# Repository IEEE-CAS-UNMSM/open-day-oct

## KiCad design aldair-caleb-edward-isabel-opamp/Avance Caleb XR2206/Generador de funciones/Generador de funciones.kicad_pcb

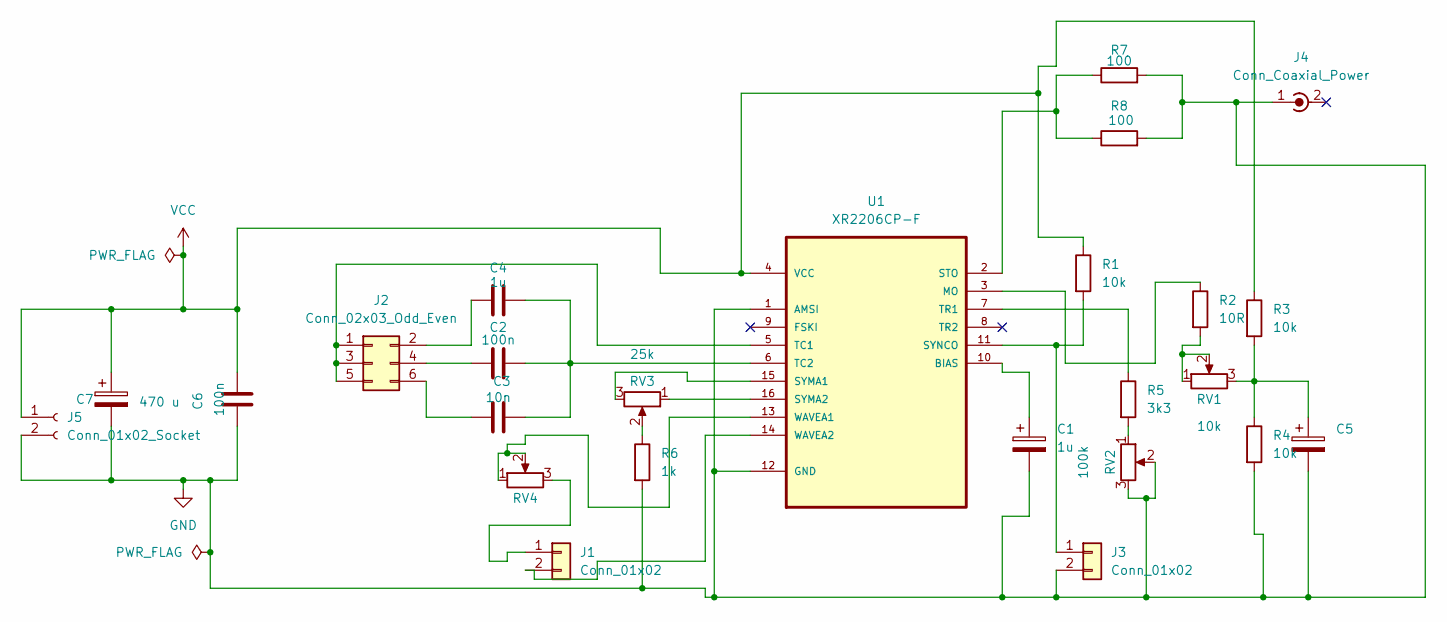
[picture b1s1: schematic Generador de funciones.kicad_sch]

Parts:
C1: 1u; CP_Radial_D4.0mm_P2.00mm
C2, C6: 100n; C_Disc_D7.0mm_W2.5mm_P5.00mm
C3: 10n; C_Disc_D7.0mm_W2.5mm_P5.00mm
C4: 1u; C_Disc_D7.0mm_W2.5mm_P5.00mm
C5: 10u; CP_Radial_D4.0mm_P2.00mm
C7: 470 u; CP_Radial_D10.0mm_P7.50mm
J1, J3: Conn_01x02; PinHeader_1x02_P2.54mm_Vertical
J2: Conn_02x03_Odd_Even; PinHeader_2x03_P2.54mm_Vertical
J4: Conn_Coaxial_Power; BNC_Amphenol_B6252HB-NPP3G-50_Horizontal
J5: Conn_01x02_Socket; PinSocket_1x02_P2.54mm_Vertical
R1, R3, R4: 10k; R_Axial_DIN0207_L6.3mm_D2.5mm_P10.16mm_Horizontal
R2: 10R; R_Axial_DIN0207_L6.3mm_D2.5mm_P10.16mm_Horizontal
R5: 3k3; R_Axial_DIN0207_L6.3mm_D2.5mm_P10.16mm_Horizontal
R6: 1k; R_Axial_DIN0207_L6.3mm_D2.5mm_P10.16mm_Horizontal
R7, R8: 100; R_Axial_DIN0207_L6.3mm_D2.5mm_P10.16mm_Horizontal
RV1: 10k; Potentiometer_Alps_RK09K_Single_Horizontal
RV2: 100k; Potentiometer_Alps_RK09K_Single_Horizontal
RV3: 25k; Potentiometer_Bourns_3266Y_Vertical
RV4: 500R; Potentiometer_Bourns_3266Y_Vertical
U1: XR2206CP-F; DIP254P762X533-16; MPN XR2206CP-F

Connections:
GND: C1.2, C5.2, C6.1, C7.2, J3.2, J4.1 (In), J5.2, R4.2, R6.2, R7.2, R8.2, RV2.2, RV2.3, U1.1 (AMSI), U1.12 (GND)
unnamed: C5.1, R3.2, R4.1, RV1.3
unnamed: J1.1, RV4.3
unnamed: J1.2, U1.14 (WAVEA2)
unnamed: J2.1, J2.3, J2.5, U1.5 (TC1)
unnamed: C4.1, J2.2
unnamed: C2.1, J2.4
unnamed: C3.1, J2.6
unnamed: J3.1, R1.2, U1.11 (SYNCO)
unnamed: R2.2, RV1.1, RV1.2
unnamed: R5.2, RV2.1
unnamed: R6.1, RV3.2
unnamed: C1.1, U1.10 (BIAS)
unnamed: R2.1, U1.3 (MO)
unnamed: R7.1, R8.1, U1.2 (STO)
unnamed: RV3.3, U1.15 (SYMA1)
unnamed: RV3.1, U1.16 (SYMA2)
unnamed: C2.2, C3.2, C4.2, U1.6 (TC2)
unnamed: R5.1, U1.7 (TR1)
unnamed: RV4.1, RV4.2, U1.13 (WAVEA1)
VCC: C6.2, C7.1, J5.1, R1.1, R3.1, U1.4 (VCC)

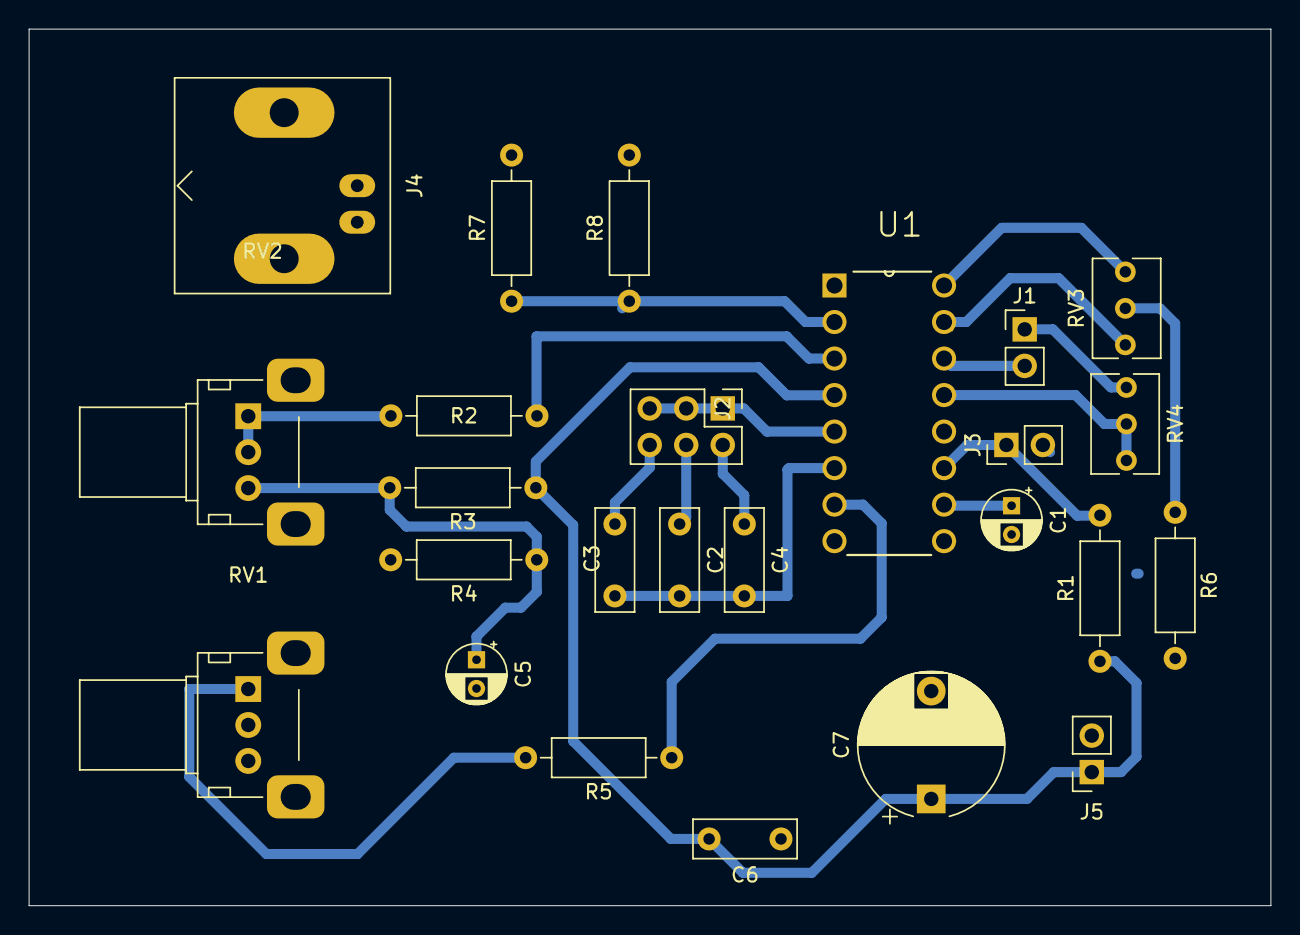
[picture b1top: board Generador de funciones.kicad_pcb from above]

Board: 2 copper layers, 86.4 x 61.0 mm, 25 parts (0 on the bottom side), 21 nets.

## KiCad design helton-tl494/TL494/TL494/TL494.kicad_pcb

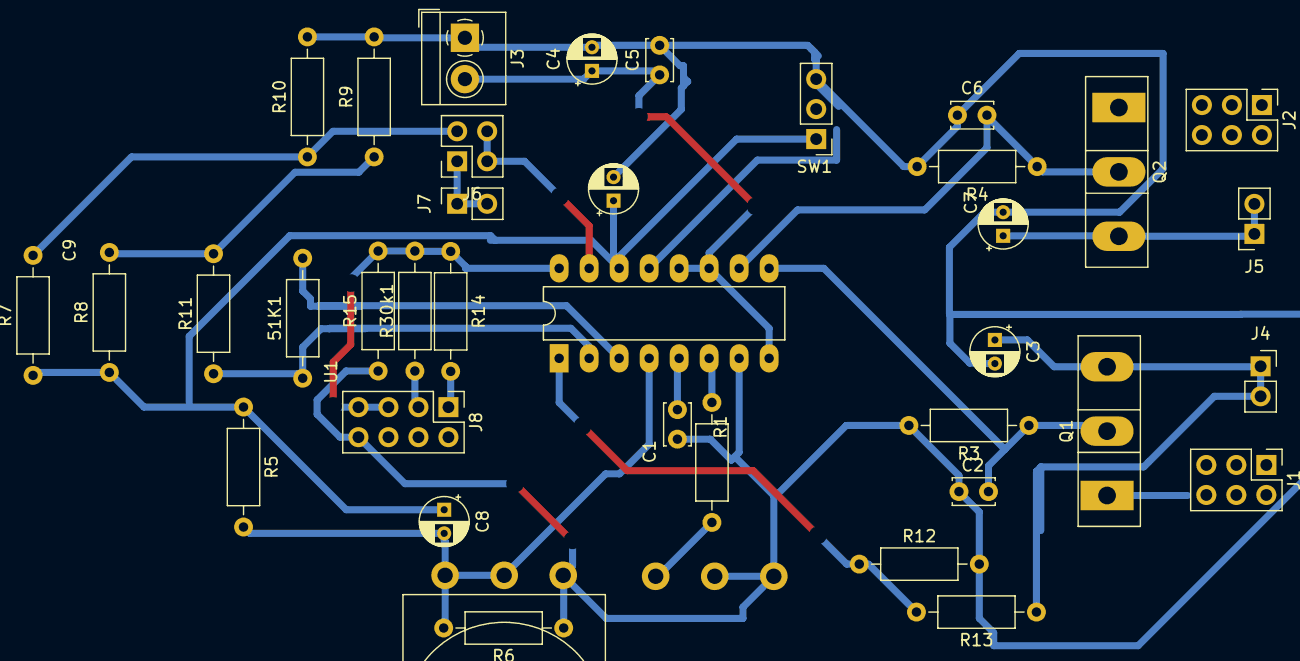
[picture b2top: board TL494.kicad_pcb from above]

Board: 2 copper layers, 39 parts (1 on the bottom side), 22 nets.

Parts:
51K1: 510; R_Axial_DIN0207_L6.3mm_D2.5mm_P10.16mm_Horizontal
C1: 1uF; C_Disc_D3.4mm_W2.1mm_P2.50mm
C2, C6: 15pF; C_Disc_D3.4mm_W2.1mm_P2.50mm
C3, C7: 10uF; CP_Radial_D4.0mm_P2.00mm
C4, C8, C9: 100uF; CP_Radial_D4.0mm_P2.00mm
C5: 10nF; C_Disc_D3.4mm_W2.1mm_P2.50mm
J1, J2: Jumper E1; PinHeader_2x03_P2.54mm_Vertical
J3: +-; TerminalBlock_4Ucon_1x02_P3.50mm_Horizontal
J4, J5, J7: Vout1; PinSocket_1x02_P2.54mm_Vertical
J6: Conn_02x02_Odd_Even; PinSocket_2x02_P2.54mm_Vertical
J8: Conn_02x04_Odd_Even; PinHeader_2x04_P2.54mm_Vertical
Q1, Q2: NMOS; TO-247-3_Vertical
R1: 2k; R_Axial_DIN0207_L6.3mm_D2.5mm_P10.16mm_Horizontal
R3, R4: 68; R_Axial_DIN0207_L6.3mm_D2.5mm_P10.16mm_Horizontal
R5: 100k; R_Axial_DIN0207_L6.3mm_D2.5mm_P10.16mm_Horizontal
R6, R10: 1k; R_Axial_DIN0207_L6.3mm_D2.5mm_P10.16mm_Horizontal
R7, R30k1: 4k; R_Axial_DIN0207_L6.3mm_D2.5mm_P10.16mm_Horizontal
R8, R9: 5.1k; R_Axial_DIN0207_L6.3mm_D2.5mm_P10.16mm_Horizontal
R11: 510; R_Axial_DIN0207_L6.3mm_D2.5mm_P10.16mm_Horizontal
R12, R14, R15: 10k; R_Axial_DIN0207_L6.3mm_D2.5mm_P10.16mm_Horizontal
R13: 50k; R_Axial_DIN0207_L6.3mm_D2.5mm_P10.16mm_Horizontal
RV1: 20k; Potentiometer_Omeg_PC16BU_Vertical
RV2: 100k; Potentiometer_Omeg_PC16BU_Vertical
SW1: CTRL; PinHeader_1x03_P2.54mm_Vertical
U1: TL494; DIP-16_W7.62mm_LongPads

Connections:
1IN+: R12.1, R13.2, U1.1 (1IN+)
1IN-: 51K1.1, R11.1, U1.2 (1IN-)
2IN+: J8.5, J8.7, R14.1, R15.2, R30k1.2, U1.16 (2IN+)
2IN-: J6.2, J6.4, U1.15 (2IN-)
CT: C1.1, U1.5 (CT)
CTRL: SW1.2 (B), U1.13 (OUTCTRL)
DTC: C8.2, R5.2, R6.2, RV2.1, RV2.2, U1.4 (DTC)
E1: C2.2, Q1.2 (G), R3.1, U1.9 (E1)
E2: C6.2, Q2.2 (G), R4.1, U1.10 (E2)
FB: 51K1.2, U1.3 (FB)
GNDREF: C1.2, C2.1, C3.2, C4.2, C5.2, C6.1, C7.2, C9.2, J3.1, J8.8, R3.2, R4.2, R6.1, R9.2, R10.2, R12.2, R15.1, RV1.1, RV1.2, RV2.3, SW1.3 (C), U1.7 (GND)
unnamed: C7.1, J5.1, J5.2, Q2.3 (S)
unnamed: J6.1, J7.1, J7.2
unnamed: J6.3, R7.2, R10.1
unnamed: J8.1, R14.2
unnamed: J8.3, R30k1.1
unnamed: R1.2, RV1.3
unnamed: R8.2, R9.1, R11.2
OUTV1: C3.1, J4.1, J4.2, Q1.3 (S), R13.1
RT: R1.1, U1.6 (RT)
VCC: C4.1, C5.1, J3.2, U1.8 (C1), U1.11 (C2), U1.12 (VCC)
VREF: C8.1, C9.1, R5.1, R7.1, R8.1, SW1.1 (A), U1.14 (REF)

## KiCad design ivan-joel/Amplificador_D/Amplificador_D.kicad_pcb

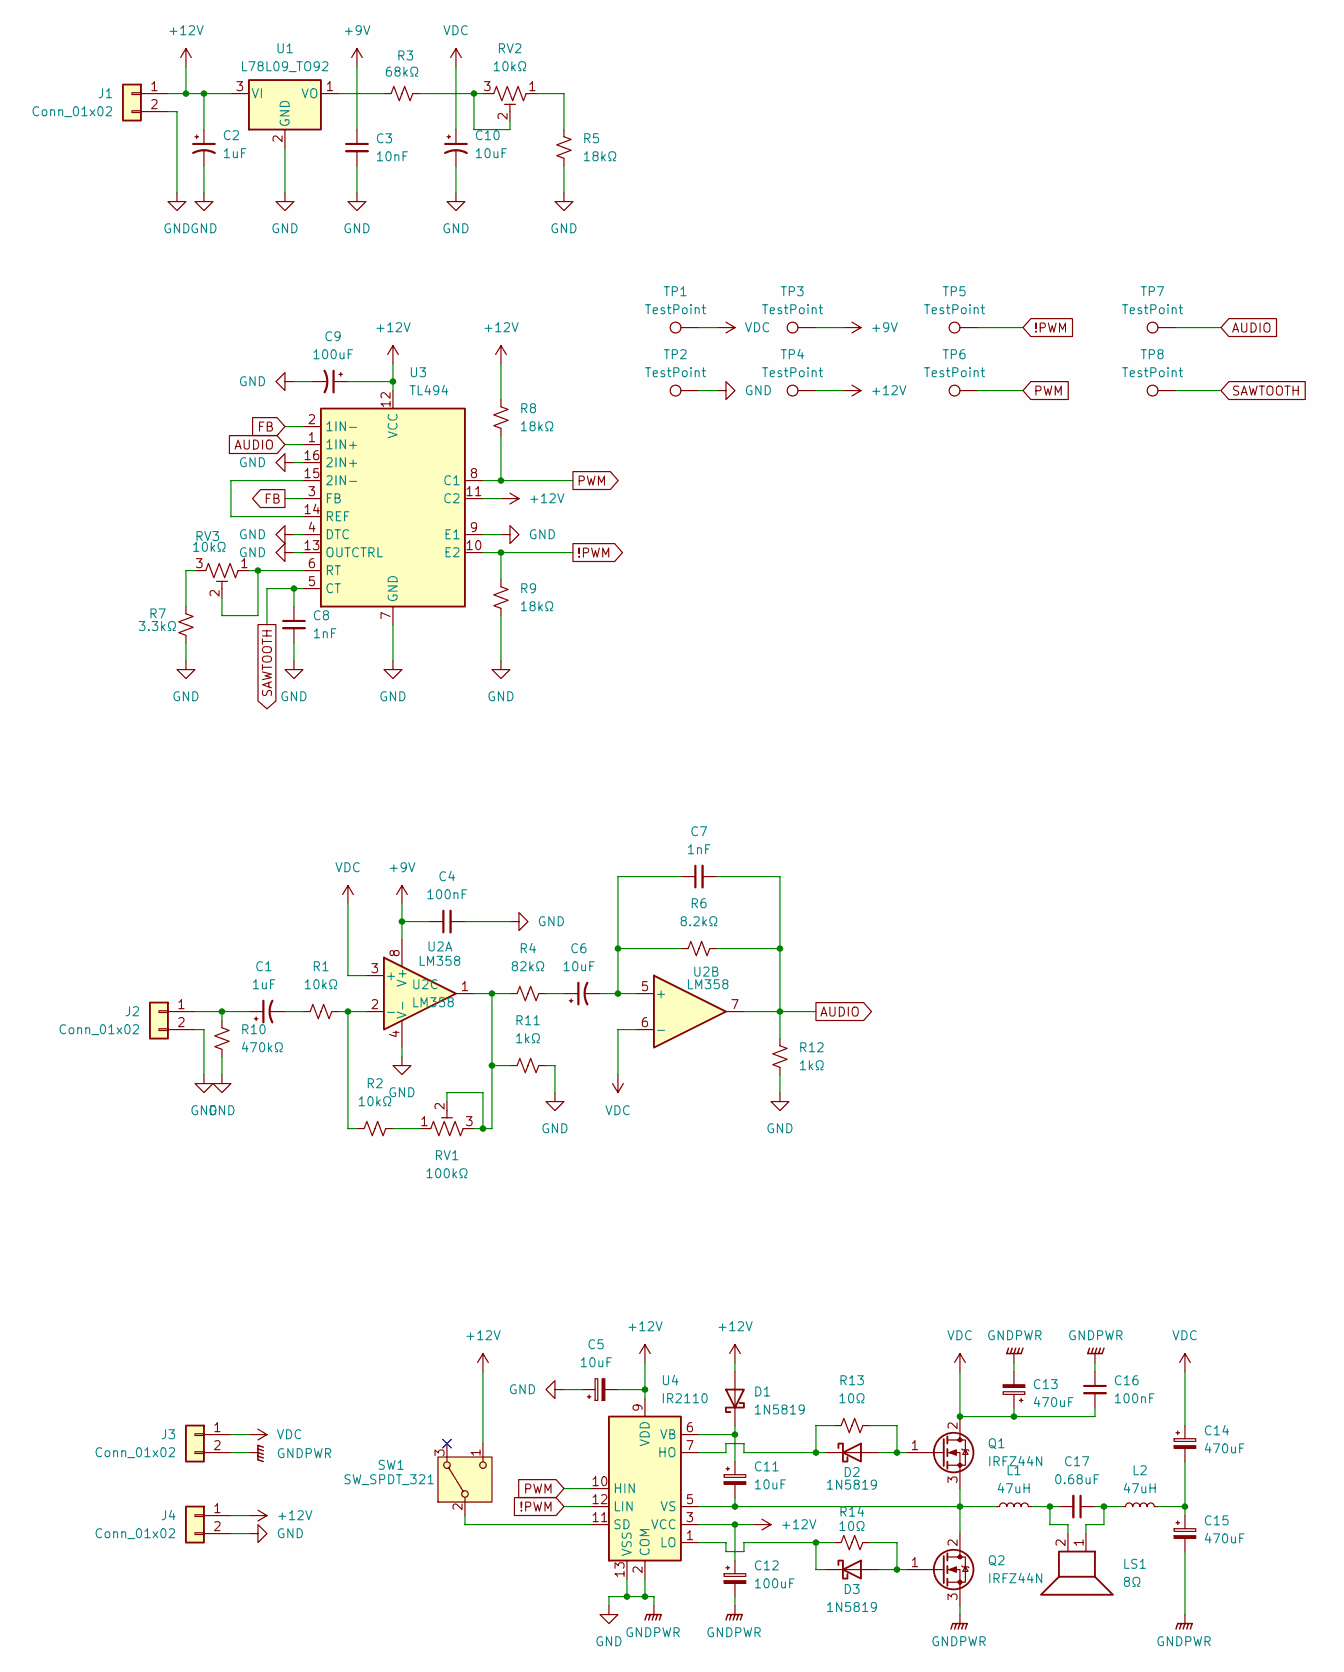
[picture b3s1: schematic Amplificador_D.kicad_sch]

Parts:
C1, C2: 1uF; CP_Radial_D5.0mm_P2.00mm
C3: 10nF; C_Disc_D3.8mm_W2.6mm_P2.50mm
C4: 100nF; C_Disc_D5.0mm_W2.5mm_P5.00mm
C5, C6, C10, C11: 10uF; CP_Radial_D5.0mm_P2.00mm
C7, C8: 1nF; C_Disc_D3.8mm_W2.6mm_P2.50mm
C9: 100uF; CP_Radial_D6.3mm_P2.50mm
C12: 100uF; CP_Radial_D8.0mm_P2.50mm
C13, C14, C15: 470uF; CP_Radial_D10.0mm_P5.00mm
C16: 100nF; C_Disc_D3.8mm_W2.6mm_P2.50mm
C17: 0.68uF; C_Rect_L7.0mm_W3.5mm_P5.00mm
D1, D2, D3: 1N5819; D_DO-41_SOD81_P10.16mm_Horizontal
J1: Conn_01x02; BarrelJack_GCT_DCJ200-10-A_Horizontal
J2, J3, J4: Conn_01x02; JST_XH_B2B-XH-A_1x02_P2.50mm_Vertical
L1, L2: 47uH; L_Radial_D12.5mm_P7.00mm_Fastron_09HCP
LS1: 8Ω; Molex_KK-396_A-41791-0002_1x02_P3.96mm_Vertical
Q1, Q2: IRFZ44N; TO-220-3_Vertical
R1, R2: 10kΩ; R_Axial_DIN0204_L3.6mm_D1.6mm_P7.62mm_Horizontal
R3: 68kΩ; R_Axial_DIN0204_L3.6mm_D1.6mm_P7.62mm_Horizontal
R4: 82kΩ; R_Axial_DIN0204_L3.6mm_D1.6mm_P7.62mm_Horizontal
R5, R8, R9: 18kΩ; R_Axial_DIN0204_L3.6mm_D1.6mm_P7.62mm_Horizontal
R6: 8.2kΩ; R_Axial_DIN0204_L3.6mm_D1.6mm_P7.62mm_Horizontal
R7: 3.3kΩ; R_Axial_DIN0204_L3.6mm_D1.6mm_P7.62mm_Horizontal
R10: 470kΩ; R_Axial_DIN0204_L3.6mm_D1.6mm_P7.62mm_Horizontal
R11, R12: 1kΩ; R_Axial_DIN0204_L3.6mm_D1.6mm_P7.62mm_Horizontal
R13, R14: 10Ω; R_Axial_DIN0204_L3.6mm_D1.6mm_P7.62mm_Horizontal
RV1: 100kΩ; Potentiometer_Bourns_3296W_Vertical
RV2, RV3: 10kΩ; Potentiometer_Bourns_3296W_Vertical
SW1: SW_SPDT_321; SW_NKK_GW12LJP
TP1, TP2, TP3, TP4, TP5, TP6, TP7, TP8: TestPoint; TestPoint_THTPad_D2.0mm_Drill1.0mm
U1: L78L09_TO92; TO-92_Inline_Wide
U2: LM358; DIP-8_W7.62mm
U3: TL494; DIP-16_W7.62mm
U4: IR2110; DIP-14_W7.62mm

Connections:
!PWM: R9.1, TP5.1, U3.10 (E2), U4.12 (LIN)
+9V: C3.1, C4.1, TP3.1, U2.8 (V+)
+12V: C2.1, C5.2, C9.1, C12.1, D1.2 (A), J1.1, J4.1, R8.1, SW1.1 (C), TP4.1, U1.3 (VI), U3.11 (C2), U3.12 (VCC), U4.3 (VCC), U4.9 (VDD)
AUDIO: C7.2, R6.2, R12.2, TP7.1, U2.7, U3.1 (1IN+)
FB: U3.2 (1IN-), U3.3 (FB)
GND: C2.2, C3.2, C4.2, C5.1, C8.2, C9.2, C10.2, C12.2, C13.2, C15.2, C16.1, J1.2, J2.2, J3.2, J4.2, Q2.3 (S), R5.2, R7.2, R9.2, R10.2, R11.2, R12.1, TP2.1, U1.2 (GND), U2.4 (V-), U3.4 (DTC), U3.7 (GND), U3.9 (E1), U3.13 (OUTCTRL), U3.16 (2IN+), U4.2 (COM), U4.13 (VSS)
unnamed: C1.2, R1.1
unnamed: C6.1, R4.2
unnamed: C14.2, C15.1, L2.2
unnamed: C17.1, L2.1, LS1.1
unnamed: C17.2, L1.2, LS1.2
unnamed: C11.1, D1.1 (K), U4.6 (VB)
unnamed: D2.2 (A), Q1.1 (G), R13.2
unnamed: D2.1 (K), R13.1, U4.7 (HO)
unnamed: D3.2 (A), Q2.1 (G), R14.2
unnamed: D3.1 (K), R14.1, U4.1 (LO)
unnamed: C1.1, J2.1, R10.1
unnamed: C11.2, L1.1, Q1.3 (S), Q2.2 (D), U4.5 (VS)
unnamed: R2.2, RV1.1
unnamed: R3.2, RV2.2, RV2.3
unnamed: R5.1, RV2.1
unnamed: R7.1, RV3.3
unnamed: R4.1, R11.1, RV1.2, RV1.3, U2.1
unnamed: SW1.2 (B), U4.11 (SD)
unnamed: R3.1, U1.1 (VO)
unnamed: R1.2, R2.1, U2.2 (-)
unnamed: C6.2, C7.1, R6.1, U2.5 (+)
unnamed: U3.14 (REF), U3.15 (2IN-)
unnamed: RV3.1, RV3.2, U3.6 (RT)
PWM: R8.2, TP6.1, U3.8 (C1), U4.10 (HIN)
SAWTOOTH: C8.1, TP8.1, U3.5 (CT)
VDC: C10.1, C13.1, C14.1, C16.2, J3.1, Q1.2 (D), TP1.1, U2.3 (+), U2.6 (-)

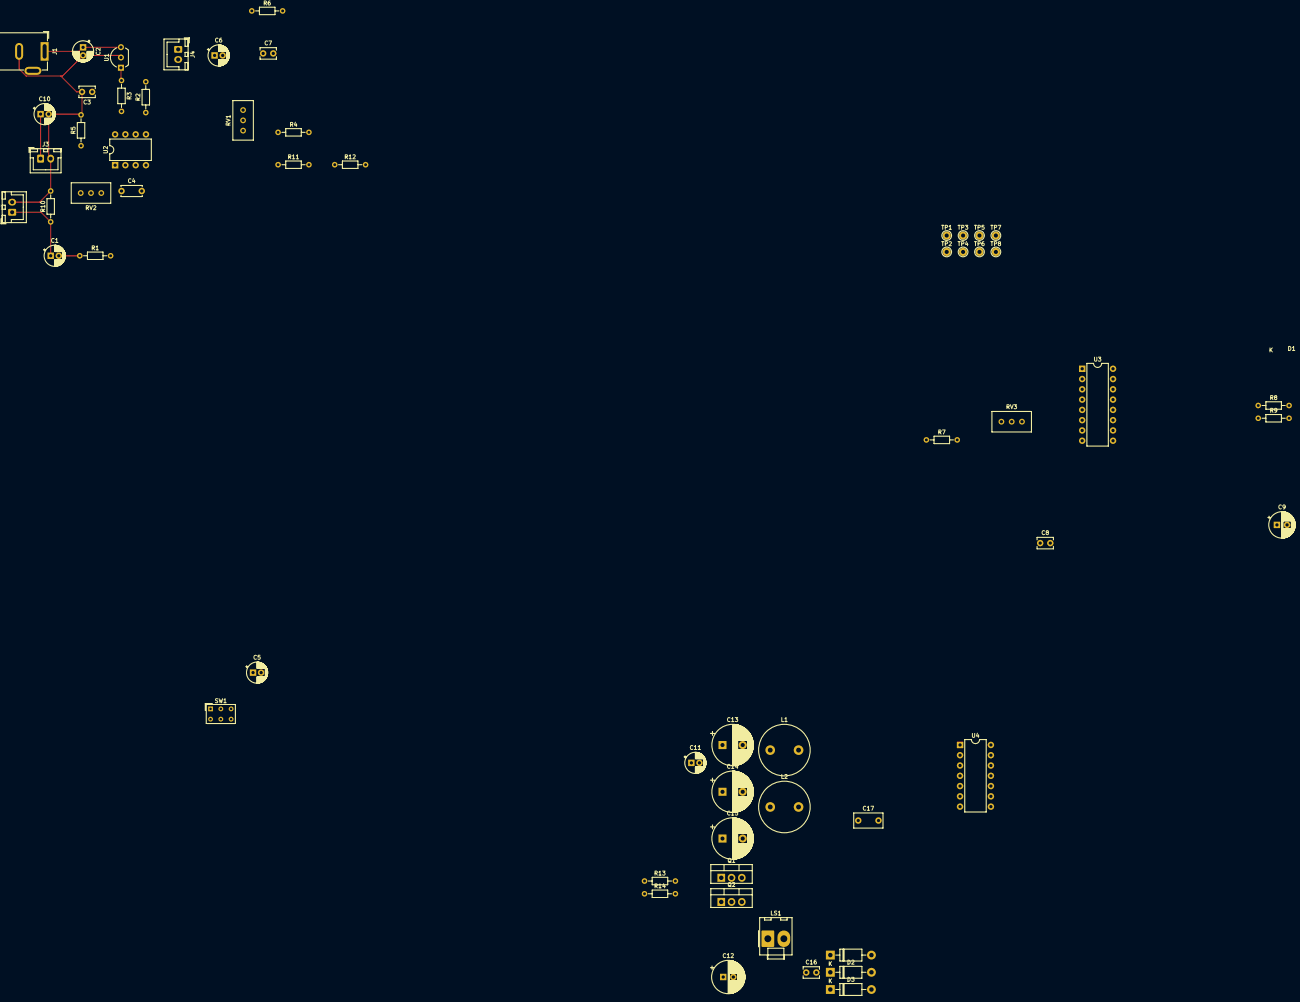
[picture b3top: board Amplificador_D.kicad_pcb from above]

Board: 2 copper layers, 59 parts (0 on the bottom side), 32 nets.

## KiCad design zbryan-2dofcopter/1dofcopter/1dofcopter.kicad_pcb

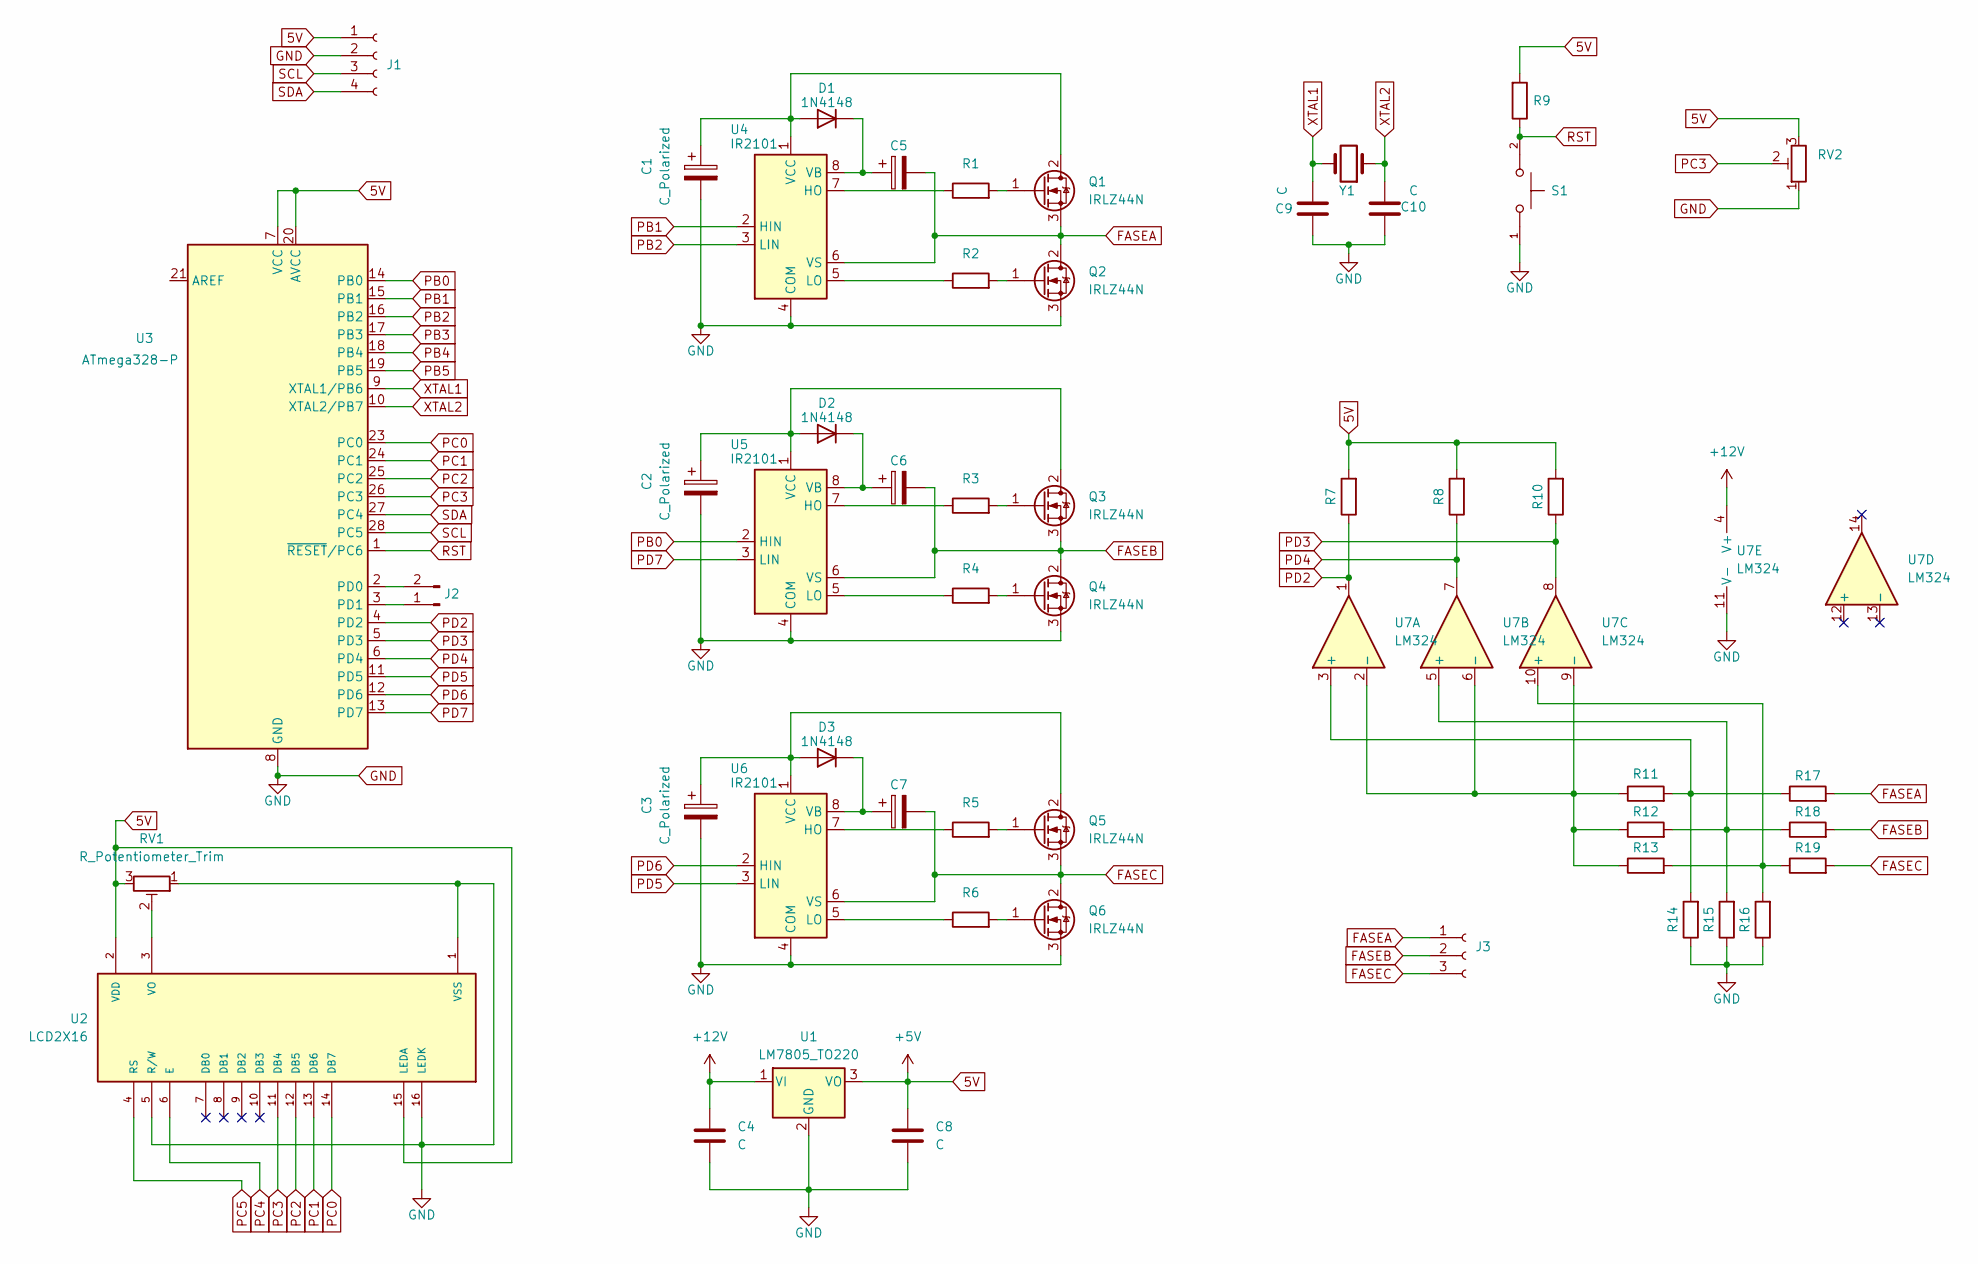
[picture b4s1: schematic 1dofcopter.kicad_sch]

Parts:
C1, C2, C3, C5, C6, C7: C_Polarized; CP_Radial_D10.0mm_P5.00mm
C4, C8: C; CP_Radial_Tantal_D9.0mm_P5.00mm
C9, C10: C; C_Disc_D9.0mm_W5.0mm_P5.00mm
D1, D2, D3: 1N4148; D_DO-35_SOD27_P7.62mm_Horizontal
J1: Conn_01x04_Socket; Molex_KK-254_AE-6410-04A_1x04_P2.54mm_Vertical
J2: Conn_01x02_Pin; PinHeader_1x02_P2.54mm_Vertical
J3: Conn_01x03_Socket; PinHeader_1x03_P2.54mm_Vertical
Q1, Q2, Q3, Q4, Q5, Q6: IRLZ44N; TO-220-3_Vertical
R1, R2, R3, R4, R5, R6, R7, R8, R9, R10, R11, R12, R13, R14, R15, R16, R17, R18, R19: R; R_Axial_DIN0207_L6.3mm_D2.5mm_P10.16mm_Horizontal
RV1, RV2: R_Potentiometer_Trim; Potentiometer_Bourns_3296Y_Vertical
S1: TL59NF160Q; SW_TL59NF160Q; PARTREV G
U1: LM7805_TO220; TO-220-3_Vertical
U2: LCD2X16; LCD_LCD2X16; PARTREV 0
U3: ATmega328-P; DIP-28_W7.62mm
U4, U5, U6: IR2101; DIP-8_W7.62mm
U7: LM324; DIP-14_W7.62mm
Y1: Crystal; Crystal_HC49-4H_Vertical

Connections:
5V: C8.1, J1.1, R7.2, R8.2, R9.2, R10.2, RV1.3, RV2.3, U1.3 (VO), U2.2 (VDD), U2.15 (LEDA), U3.7 (VCC), U3.20 (AVCC)
+12V: C4.1, U1.1 (VI), U7.4 (V+)
FASEA: C5.2, J3.1, Q1.3 (S), Q2.2 (D), R17.2, U4.6 (VS)
FASEB: C6.2, J3.2, Q3.3 (S), Q4.2 (D), R18.2, U5.6 (VS)
FASEC: C7.2, J3.3, Q5.3 (S), Q6.2 (D), R19.2, U6.6 (VS)
GND: C1.2, C2.2, C3.2, C4.2, C8.2, C9.1, C10.2, J1.2, Q2.3 (S), Q4.3 (S), Q6.3 (S), R14.1, R15.1, R16.1, RV1.1, RV2.1, S1.1, U1.2 (GND), U2.1 (VSS), U2.5 (R/W), U2.16 (LEDK), U3.8 (GND), U3.22 (GND), U4.4 (COM), U5.4 (COM), U6.4 (COM), U7.11 (V-)
unnamed: C1.1, D1.2 (A), Q1.2 (D), U4.1 (VCC)
unnamed: C5.1, D1.1 (K), U4.8 (VB)
unnamed: C2.1, D2.2 (A), Q3.2 (D), U5.1 (VCC)
unnamed: C6.1, D2.1 (K), U5.8 (VB)
unnamed: C3.1, D3.2 (A), Q5.2 (D), U6.1 (VCC)
unnamed: C7.1, D3.1 (K), U6.8 (VB)
unnamed: J2.1, U3.3 (PD1)
unnamed: J2.2, U3.2 (PD0)
unnamed: Q1.1 (G), R1.2
unnamed: Q2.1 (G), R2.2
unnamed: Q3.1 (G), R3.2
unnamed: Q4.1 (G), R4.2
unnamed: Q5.1 (G), R5.2
unnamed: Q6.1 (G), R6.2
unnamed: RV1.2, U2.3 (VO)
unnamed: R1.1, U4.7 (HO)
unnamed: R2.1, U4.5 (LO)
unnamed: R3.1, U5.7 (HO)
unnamed: R4.1, U5.5 (LO)
unnamed: R5.1, U6.7 (HO)
unnamed: R6.1, U6.5 (LO)
unnamed: R11.2, R14.2, R17.1, U7.3 (+)
unnamed: R11.1, R12.1, R13.1, U7.2 (-), U7.6 (-), U7.9 (-)
unnamed: R12.2, R15.2, R18.1, U7.5 (+)
unnamed: R13.2, R16.2, R19.1, U7.10 (+)
PB0: U3.14 (PB0), U5.2 (HIN)
PB1: U3.15 (PB1), U4.2 (HIN)
PB2: U3.16 (PB2), U4.3 (LIN)
PB3: U3.17 (PB3)
PB4: U3.18 (PB4)
PB5: U3.19 (PB5)
PC0: U2.14 (DB7), U3.23 (PC0)
PC1: U2.13 (DB6), U3.24 (PC1)
PC2: U2.12 (DB5), U3.25 (PC2)
PC3: RV2.2, U2.11 (DB4), U3.26 (PC3)
PC4: U2.6 (E)
PC5: U2.4 (RS)
PD2: R7.1, U3.4 (PD2), U7.1
PD3: R10.1, U3.5 (PD3), U7.8
PD4: R8.1, U3.6 (PD4), U7.7
PD5: U3.11 (PD5), U6.3 (LIN)
PD6: U3.12 (PD6), U6.2 (HIN)
PD7: U3.13 (PD7), U5.3 (LIN)
RST: R9.1, S1.2, U3.1 (~RESET/PC6)
SCL: J1.3, U3.28 (PC5)
SDA: J1.4, U3.27 (PC4)
XTAL1: C9.2, U3.9 (XTAL1/PB6), Y1.2
XTAL2: C10.1, U3.10 (XTAL2/PB7), Y1.1

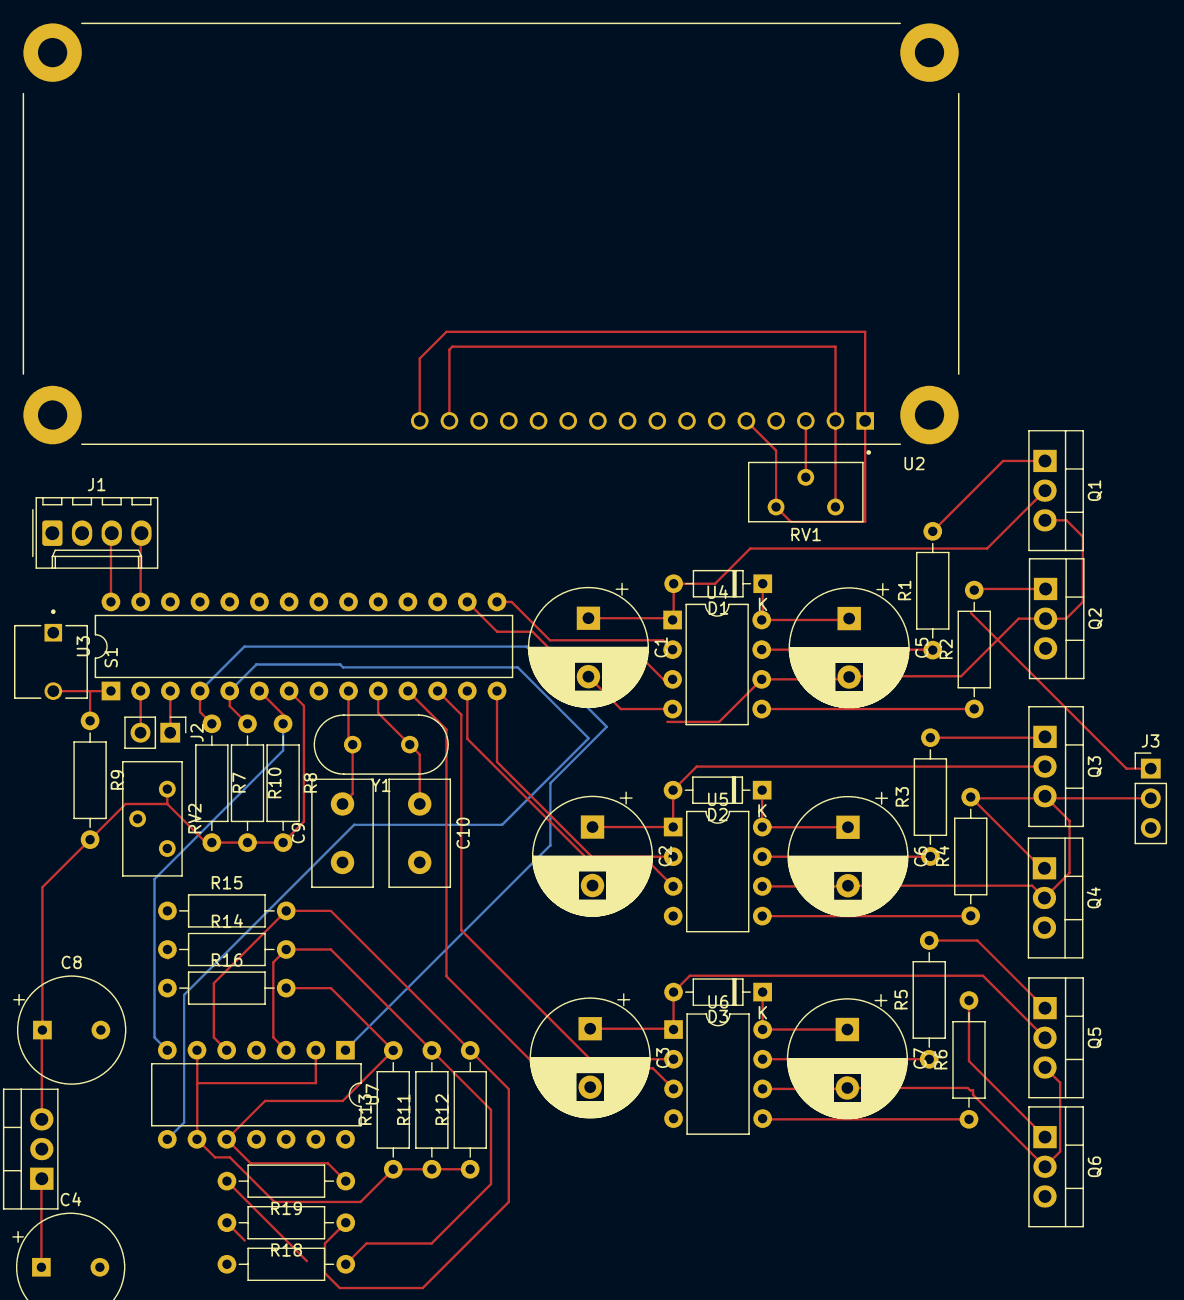
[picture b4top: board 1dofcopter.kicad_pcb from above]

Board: 2 copper layers, 52 parts (0 on the bottom side), 49 nets.

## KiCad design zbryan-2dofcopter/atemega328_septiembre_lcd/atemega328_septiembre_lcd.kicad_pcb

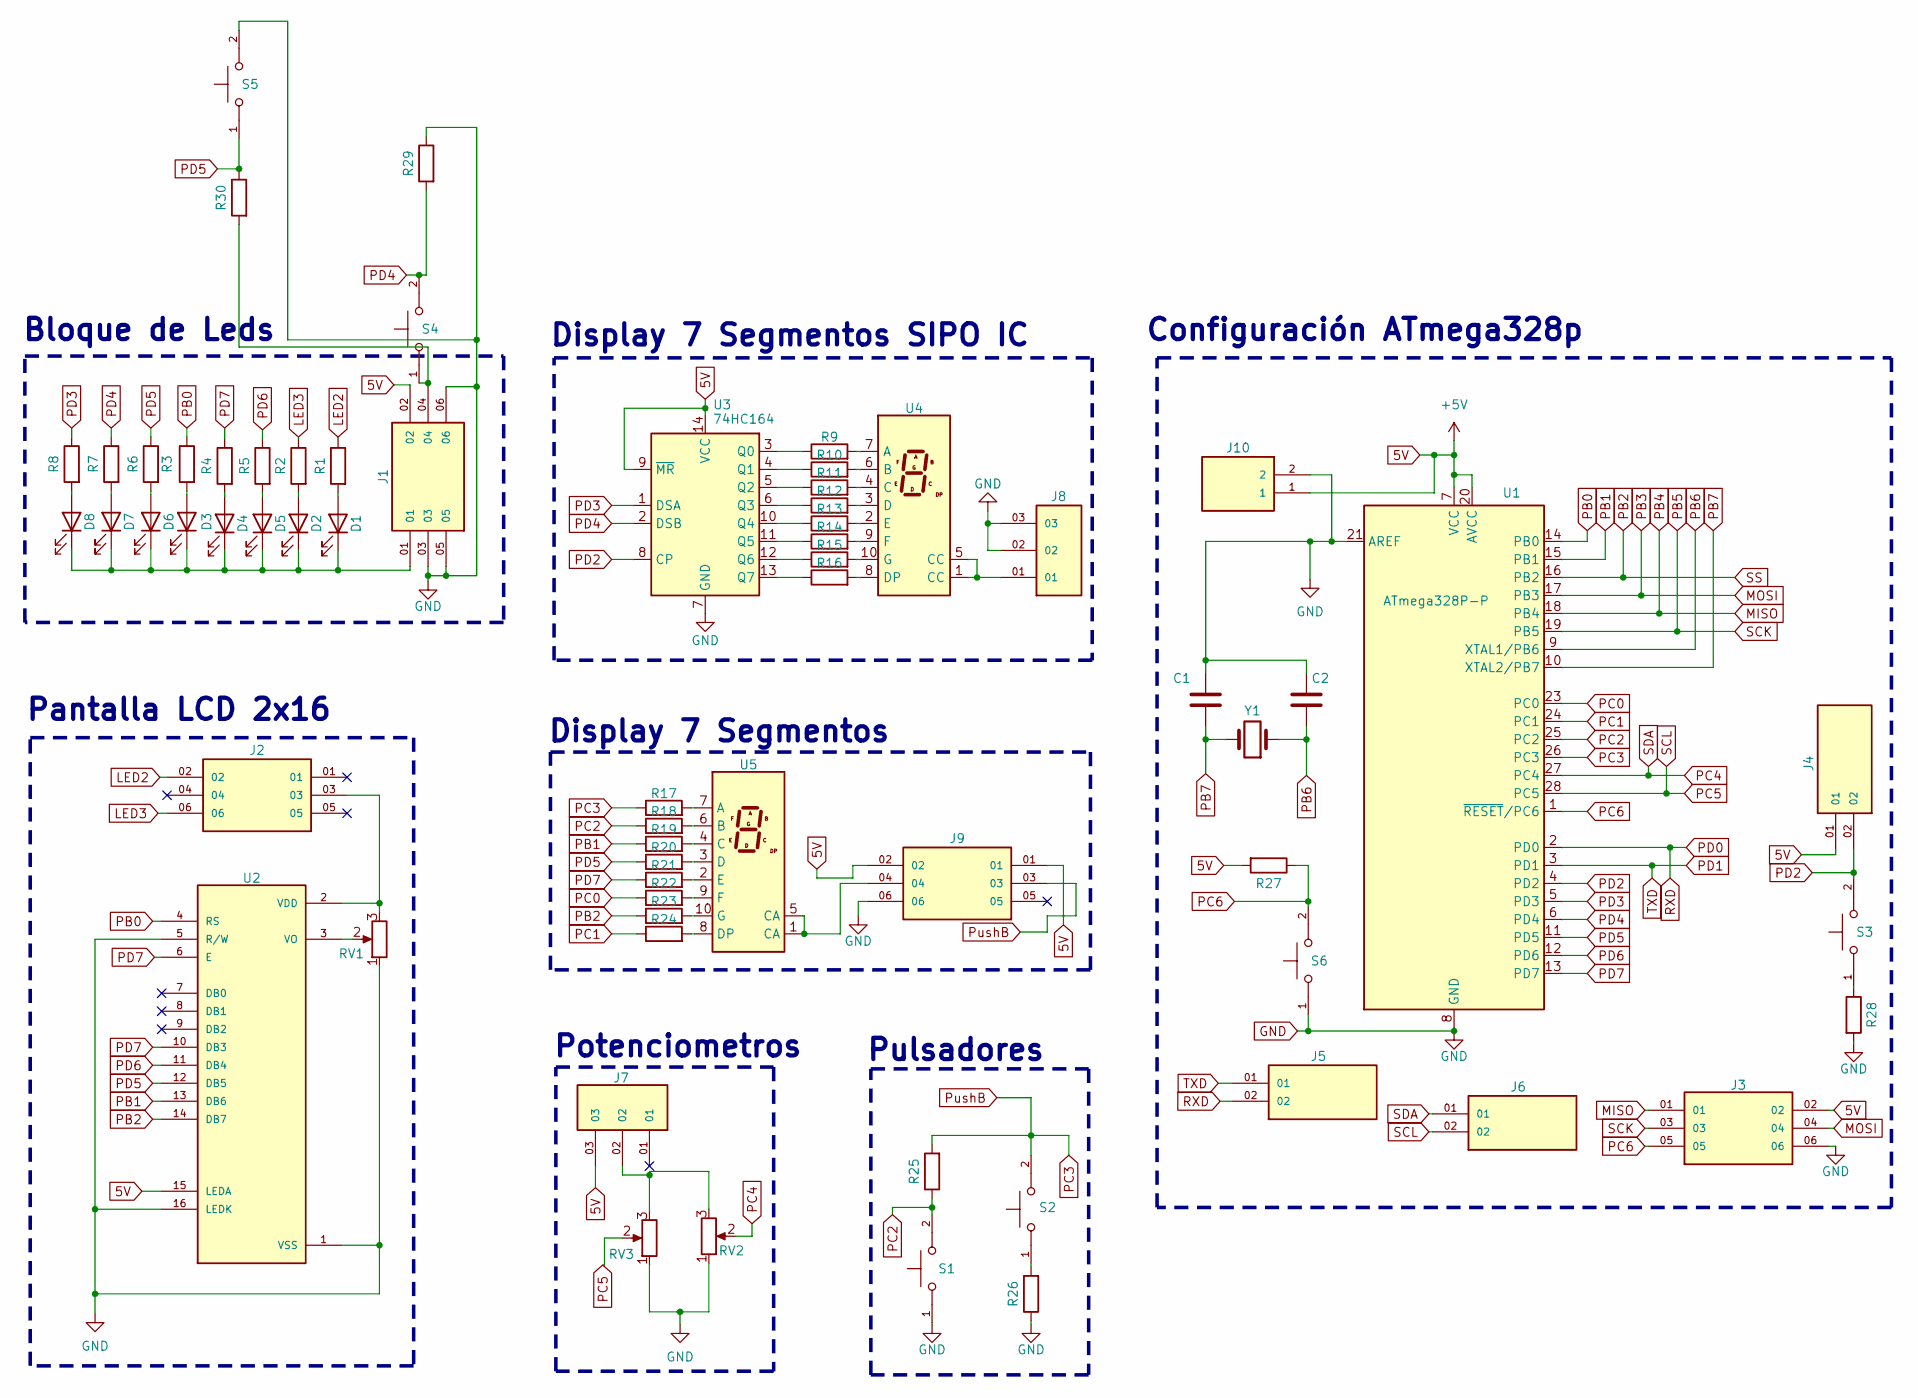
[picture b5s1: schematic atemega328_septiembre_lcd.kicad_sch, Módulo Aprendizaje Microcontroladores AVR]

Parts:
C1, C2: C; C_Disc_D5.0mm_W2.5mm_P2.50mm
D1, D2, D3, D4, D5, D6, D7, D8: LED; LED_D5.0mm
J1, J2, J3, J9: TSW-103-17-T-D; SAMTEC_TSW-103-17-T-D; PARTREV R
J4, J5, J6: TSW-102-09-G-S; SAMTEC_TSW-102-09-G-S; PARTREV R
J7, J8: TSW-101-26-S-T; SAMTEC_TSW-101-26-S-T; PARTREV R
J10: TB010-508-02BE; CUI_TB010-508-02BE
R1, R2, R3, R4, R5, R6, R7, R8, R13, R14, R15, R16, R17, R18, R19, R20, R21, R22, R23, R24, R25, R26, R27, R28: R; R_Axial_DIN0204_L3.6mm_D1.6mm_P7.62mm_Horizontal
R9, R10, R11, R12, R29, R30: R; R_Axial_DIN0207_L6.3mm_D2.5mm_P7.62mm_Horizontal
RV1, RV2, RV3: R_Potentiometer; Potentiometer_Bourns_3339P_Vertical
S1, S2, S3, S4, S5, S6: TL59NF160Q; SW_TL59NF160Q; PARTREV G
U1: ATmega328P-P; DIP-28_W7.62mm
U2: LCD2X16; LCD_LCD2X16; PARTREV 0
U3: 74HC164; DIP-14_W7.62mm
U4: SBC18-11EGWA; SC56-11SRWA_KNB
U5: SA15-11SRWA; SC56-11SRWA_KNB
Y1: Crystal; Crystal_HC49-4H_Vertical

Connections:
5V: J1.02, J3.02, J4.01, J7.03, J9.01, J9.02, J10.1, R27.2, U1.7 (VCC), U1.20 (AVCC), U2.15 (LEDA), U3.9 (~MR), U3.14 (VCC)
GND: C1.2, C2.2, J1.03, J1.05, J1.06, J3.06, J8.02, J8.03, J9.06, J10.2, R26.1, R28.2, R29.1, RV1.1, RV2.1, RV3.1, S1.1, S5.2, S6.1, U1.8 (GND), U1.21 (AREF), U1.22 (GND), U2.1 (VSS), U2.5 (R/W), U2.16 (LEDK), U3.7 (GND)
LED2: J2.02, R1.1
LED3: J2.06, R2.1
MISO: J3.01, U1.18 (PB4)
MOSI: J3.04, U1.17 (PB3)
unnamed: D1.2 (A), R1.2
unnamed: D1.1 (K), D2.1 (K), D3.1 (K), D4.1 (K), D5.1 (K), D6.1 (K), D7.1 (K), D8.1 (K), J1.01
unnamed: D2.2 (A), R2.2
unnamed: D3.2 (A), R3.2
unnamed: D4.2 (A), R4.2
unnamed: D5.2 (A), R5.2
unnamed: D6.2 (A), R6.2
unnamed: D7.2 (A), R7.2
unnamed: D8.2 (A), R8.2
unnamed: J1.04, R30.2, S4.1
unnamed: J7.02, RV2.3, RV3.3
unnamed: J8.01, U4.1 (CC), U4.5 (CC)
unnamed: J9.04, U5.1 (CA), U5.5 (CA)
unnamed: R26.2, S2.1
unnamed: R28.1, S3.1
unnamed: J2.03, RV1.3, U2.2 (VDD)
unnamed: RV1.2, U2.3 (VO)
unnamed: R9.1, U3.3 (Q0)
unnamed: R10.1, U3.4 (Q1)
unnamed: R11.1, U3.5 (Q2)
unnamed: R12.1, U3.6 (Q3)
unnamed: R13.1, U3.10 (Q4)
unnamed: R14.1, U3.11 (Q5)
unnamed: R15.1, U3.12 (Q6)
unnamed: R16.1, U3.13 (Q7)
unnamed: R9.2, U4.7 (A)
unnamed: R10.2, U4.6 (B)
unnamed: R11.2, U4.4 (C)
unnamed: R12.2, U4.3 (D)
unnamed: R16.2, U4.8 (DP)
unnamed: R13.2, U4.2 (E)
unnamed: R14.2, U4.9 (F)
unnamed: R15.2, U4.10 (G)
unnamed: R17.2, U5.7 (A)
unnamed: R18.2, U5.6 (B)
unnamed: R19.2, U5.4 (C)
unnamed: R20.2, U5.3 (D)
unnamed: R24.2, U5.8 (DP)
unnamed: R21.2, U5.2 (E)
unnamed: R22.2, U5.9 (F)
unnamed: R23.2, U5.10 (G)
PB0: R3.1, U1.14 (PB0), U2.4 (RS)
PB1: R19.1, U1.15 (PB1), U2.13 (DB6)
PB2: R23.1, U1.16 (PB2), U2.14 (DB7)
PB5: J3.03, U1.19 (PB5)
PB6: C2.1, U1.9 (XTAL1/PB6), Y1.1
PB7: C1.1, U1.10 (XTAL2/PB7), Y1.2
PC0: R22.1, U1.23 (PC0)
PC1: R24.1, U1.24 (PC1)
PC2: R18.1, R25.1, S1.2, U1.25 (PC2)
PC3: J9.03, R17.1, R25.2, S2.2, U1.26 (PC3)
PC4: J6.01, RV2.2, U1.27 (PC4)
PC5: J6.02, RV3.2, U1.28 (PC5)
PC6: J3.05, R27.1, S6.2, U1.1 (~RESET/PC6)
PD0: J5.02, U1.2 (PD0)
PD1: J5.01, U1.3 (PD1)
PD2: J4.02, S3.2, U1.4 (PD2), U3.8 (CP)
PD3: R8.1, U1.5 (PD3), U3.1 (DSA)
PD4: R7.1, R29.2, S4.2, U1.6 (PD4), U3.2 (DSB)
PD5: R6.1, R20.1, R30.1, S5.1, U1.11 (PD5), U2.12 (DB5)
PD6: R5.1, U1.12 (PD6), U2.11 (DB4)
PD7: R4.1, R21.1, U1.13 (PD7), U2.6 (E), U2.10 (DB3)

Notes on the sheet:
Display 7 Segmentos SIPO IC
Bloque de Leds
Potenciometros
Display 7 Segmentos
Configuración ATmega328p
Pulsadores
Pantalla LCD 2x16
